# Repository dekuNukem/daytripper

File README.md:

# Daytripper: Hide-My-Windows Laser Tripwire

[Buy on Tindie](https://www.tindie.com/products/dekuNukem/daytripper-hide-my-windows-laser-tripwire/) | [Official Discord](https://discord.gg/VM4kbnf) | [Getting Started](quick_start_guide.md)

-----

Do you always slack off on your computer and worry about getting busted?

Not anymore because Daytripper is here to save the day!

Daytripper is a laser tripwire that can, upon triggering:

* Hide all your windows
* Lock your computer
* [Execute a custom script](/advanced_usage.md) to do whatever you want!

## Buy Daytripper on Tindie!

I did a small production run, and you can buy them directly on Tindie:

https://www.tindie.com/products/dekuNukem/daytripper

## How it Works

Daytripper comes in two parts: a Transmitter (TX) and a Receiver (RX).

Mount the TX in the path of incoming threat. Plug RX into your computer.

When motion is detected, RX will press `Win + M` and instantly hide what you're doing.

Alternatively, it can also lock your PC or [execute a custom script](/advanced_usage.md).

## Features

Daytripper...

* Can detect motion within 120cm (4 ft).

* Scan rate: 6Hz on battery, 30Hz while powered. Customisable with included software.

* Configurable parameters to suit your particular needs.

* 50-hour battery life, rechargeable via USB-C.

* Works out-of-box with Windows, compatible with all major OSs.

* 100 meter (330 ft) open-air communication range between TX and RX.

* Comes with a magnetic mounting kit.

* See [Quick Start Guide](https://github.com/dekuNukem/daytripper/blob/master/quick_start_guide.md) and [Advanced Usage Guide](https://github.com/dekuNukem/daytripper/blob/master/advanced_usage.md) for more details.

## Getting Started

If you received your Daytripper in kit form, follow this to put it together:

[Kit Assembly Guide](/assembly_guide.md)

For how to use Daytripper, see this:

[Quick Start Guide](/quick_start_guide.md)

For advanced features such as custom actions and adjusting settings, read this:

[Advanced Usage](/advanced_usage.md)

## Specification

## FAQ

### What operating system is supported?

Daytripper works out-of-box with Windows. No driver needed.

It is also compatible with anything that supports USB keyboards, such as Linux, MacOS, Android, and more.

Read [Advanced Usage Guide](/advanced_usage.md) to see how to use it on other systems.

### What is the range of Daytripper?

The laser ToF sensor can detect motion within 120cm (4 ft).

The wireless communication range between TX and RX should be around 100 meters (330 feet) open air. Might be less in indoor environments. 

### Battery life?

Around 50 hours (more than 2 days!) with default configuration.

Can be increased or decreased by adjusting settings.

Rechargeable via USB Type-C connector.

### Can I use it for purposes other than hiding windows?

Yes. It can also lock your computer, or perform a custom action.

See [Advanced Usage Guide](/advanced_usage.md).

## I Want One!

I did a small production run, and you can buy them directly on Tindie:

https://www.tindie.com/products/dekuNukem/daytripper

## Questions or Comments?

Please feel free to [open an issue](https://github.com/dekuNukem/duckypad/issues), ask in the [official Daytripper discord](https://discord.gg/VM4kbnf), DM me on discord `dekuNukem#6998`, or email `dekuNukem`@`gmail`.`com` for inquires.

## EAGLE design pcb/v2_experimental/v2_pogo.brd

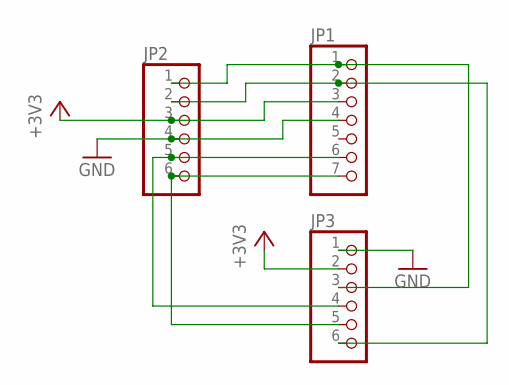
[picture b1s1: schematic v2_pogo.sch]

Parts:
JP1: PINHD-1X7; 1X07
JP2, JP3: PINHD-1X6; 1X06

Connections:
+3V3: JP1.3, JP2.3, JP3.2
GND: JP1.4, JP2.4, JP3.1
unnamed: JP1.7, JP2.6, JP3.5
unnamed: JP1.6, JP2.5, JP3.4
unnamed: JP1.2, JP2.2, JP3.6
unnamed: JP1.1, JP2.1, JP3.3

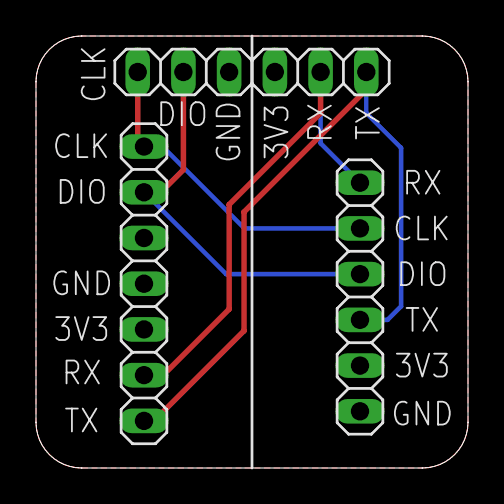
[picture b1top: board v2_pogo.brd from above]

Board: 2 copper layers, 24.0 x 24.0 mm, 3 parts (0 on the bottom side), 6 nets.

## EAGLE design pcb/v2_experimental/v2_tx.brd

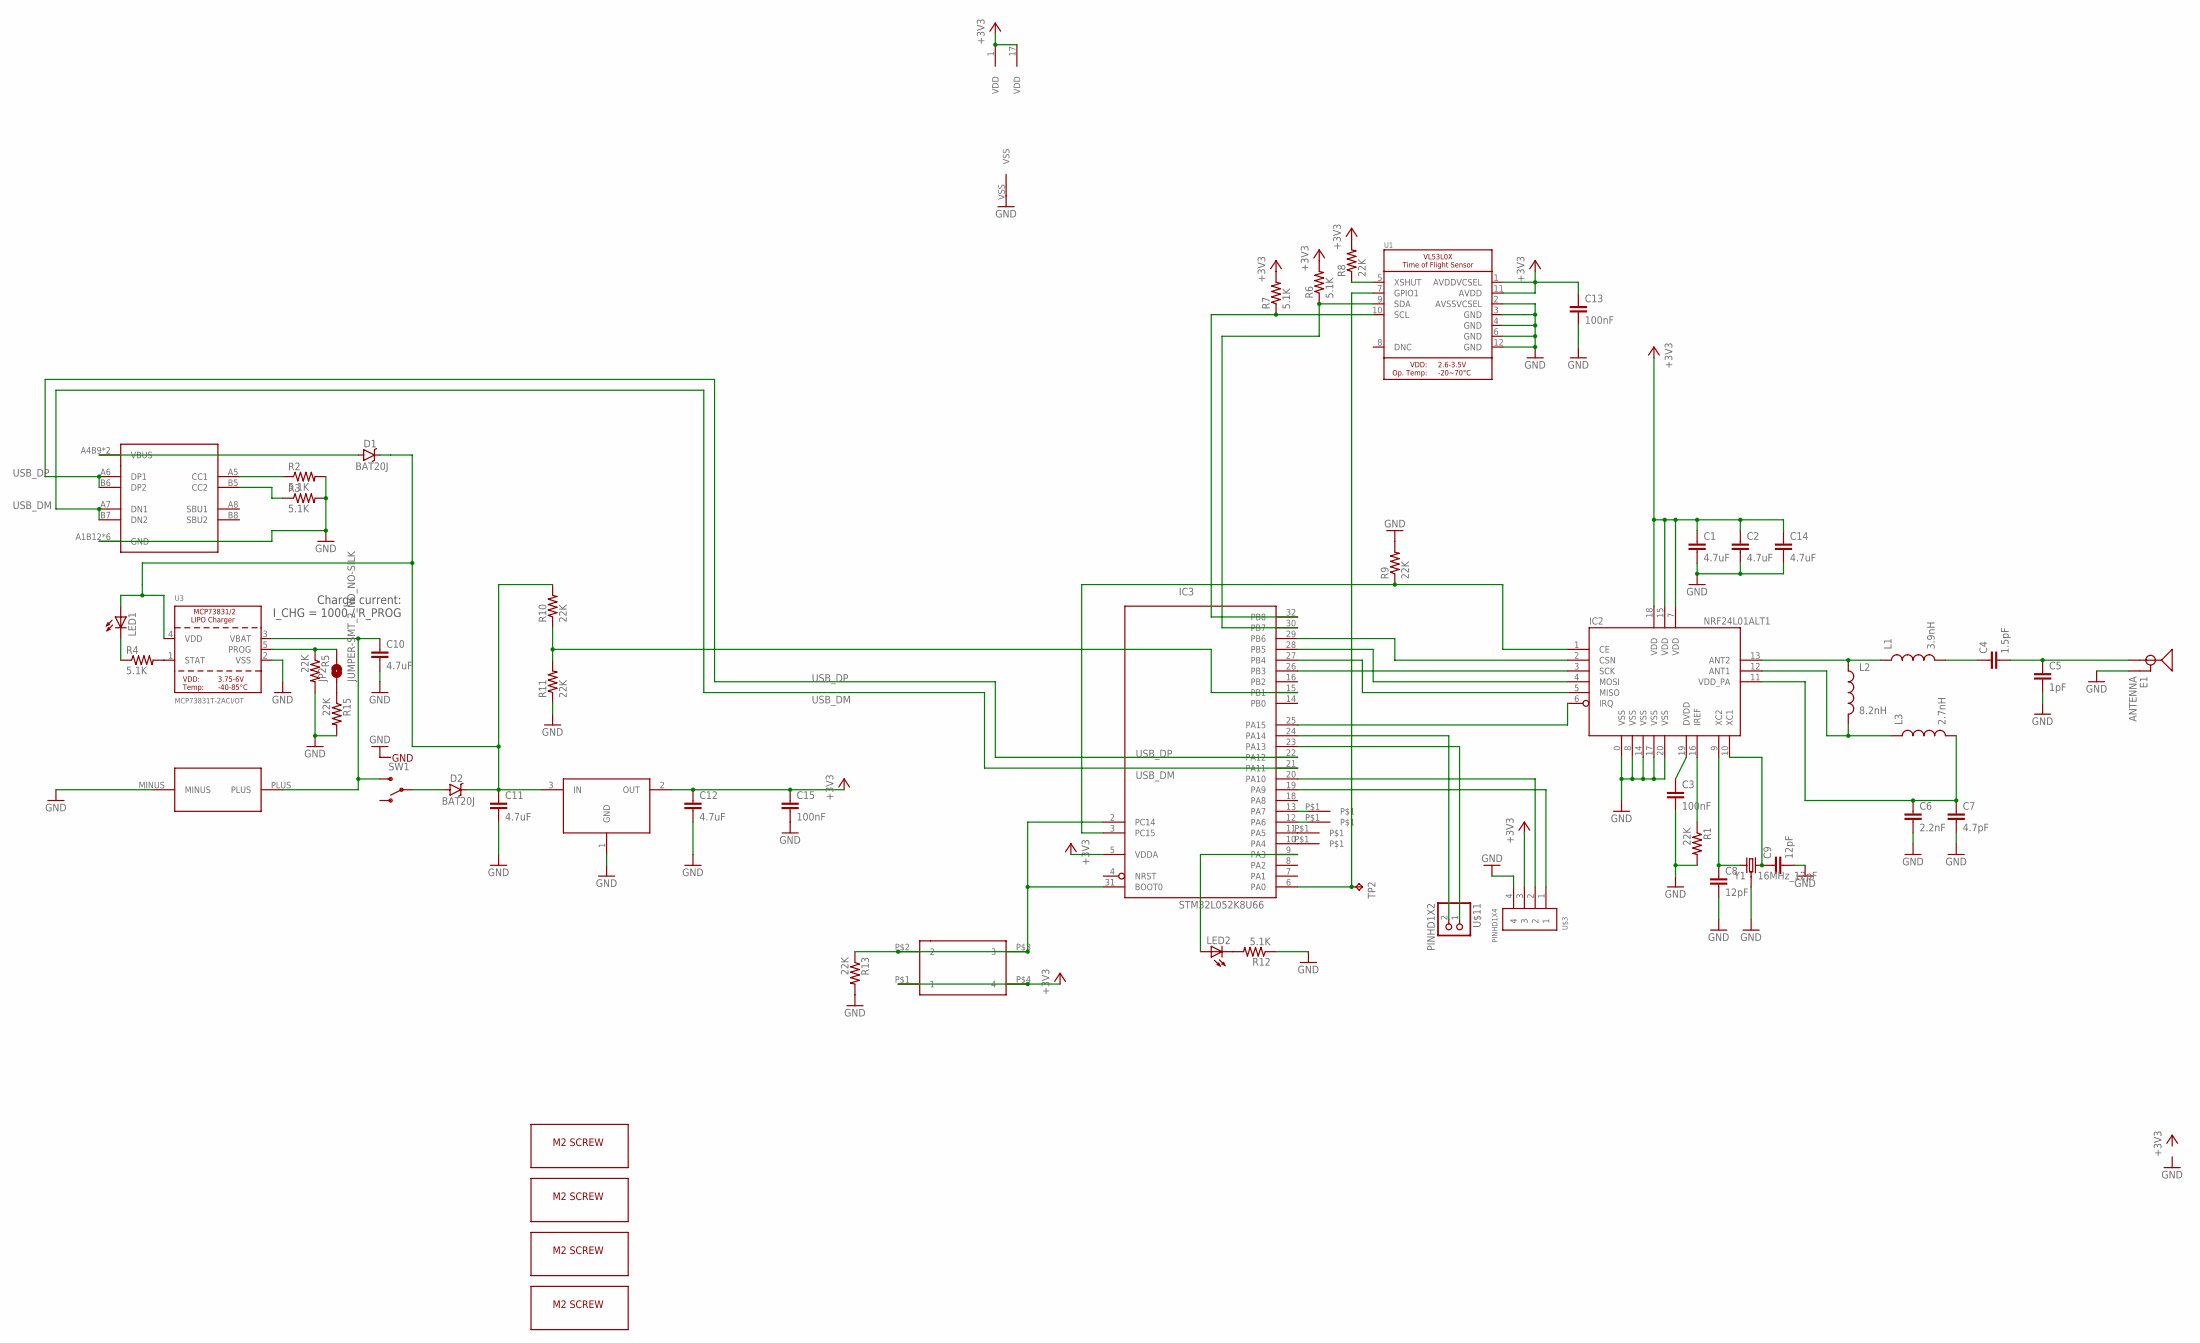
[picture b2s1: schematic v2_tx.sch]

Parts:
C1, C2, C10, C11, C12, C14: 4.7uF; 0805
C3, C13, C15: 100nF; 0805
C4: 1.5pF; 0805
C5: 1pF; 0805
C6: 2.2nF; 0805
C7: 4.7pF; 0805
C8, C9: 12pF; 0805
D1, D2: BAT20J; SOD-323
E1: ANTENNA; TRACE_ANTENNA_2.4GHZ_25.7MM_TUNED
IC2: NRF24L01ALT1; QFN20_ALT1
IC3: STM32L052K8U66; UFQFPN32
JP2: JUMPER-SMT_2_NO_NO-SILK; SMT-JUMPER_2_NO_NO-SILK
L1: 3.9nH; 0805
L2: 8.2nH; 0805
L3: 2.7nH; 0805
LED1, LED2: LEDCHIP-LED0805; CHIP-LED0805
R1, R5, R8, R9, R10, R11, R13, R15: 22K; 0805
R2, R3, R4, R6, R7, R12: 5.1K; 0805
SW1: SWITCH-SPDTTDFGDFG; SWITCH-SPST-SMD-A
SW2: 324_SW324_SWITCH_FOOT_HOLE; 342_SWICH_FOOT_HOLE
TP2: TPTP10R; TP10R
U1: VL53L0X; LGA12_ST
U2: USBC_16P; USBC_16P_FOOT
U3: MCP73831T-2ACI/OT; SOT23-5
U4: XC6206_DEV; SOT23R_INFINEON
U$1, U$12, U$13, U$14: M2_SCREW_DEV; M2_SCREW_FOOT
U$2: HOT_SWAP_COIN_BAT; COIN_BAT_HOTSWAP_SOCKET
U$3: PINHD1X4; 1X04-CLEANBIG
U$4, U$5, U$6, U$7: TESTPAD
U$11: PINHD1X2; 1X02
Y1: 16MHz_12pF; CRYSTAL-SMD-3.2X2.5MM

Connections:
+3V3: C1.1, C2.1, C12.1, C13.1, C14.1, C15.1, IC2.7 (VDD), IC2.15 (VDD), IC2.18 (VDD), IC3.1 (VDD), IC3.5 (VDDA), IC3.17 (VDD), R6.2, R7.2, R8.2, SW2.P$1 (1), SW2.P$4 (4), U1.1 (AVDDVCSEL), U1.11 (AVDD), U4.2 (OUT), U$3.3
GND: C1.2, C2.2, C3.2, C5.2, C6.2, C7.2, C8.2, C9.2, C10.2, C11.2, C12.2, C13.2, C14.2, C15.2, E1.GND, E1.GND2 (GND), IC2.0 (VSS), IC2.8 (VSS), IC2.14 (VSS), IC2.17 (VSS), IC2.20 (VSS), IC3.VSS, R1.2, R2.2, R3.2, R5.2, R9.2, R11.1, R12.1, R13.2, R15.2, SW1.G1 (GND), SW1.G2 (GND), SW1.G3 (GND), SW1.G4 (GND), U1.2 (AVSSVCSEL), U1.3 (GND), U1.4 (GND), U1.6 (GND), U1.12 (GND), U2.A1B12 (GND), U2.B11A12 (GND), U2.P$13 (GND), U2.P$14 (GND), U2.P$15 (GND), U2.P$16 (GND), U3.2 (VSS), U4.1 (GND), U$2.MINUS, U$3.4, Y1.2 (3), Y1.4 (3)
unnamed: C3.1, IC2.19 (DVDD)
unnamed: IC2.16 (IREF), R1.1
unnamed: IC2.13 (ANT2), L1.1, L2.1
unnamed: C4.1, L1.2
unnamed: C4.2, C5.1, E1.ANT (SIGNAL)
unnamed: IC2.12 (ANT1), L2.2, L3.1
unnamed: C8.1, IC2.9 (XC2), Y1.1
unnamed: C6.1, C7.1, IC2.11 (VDD_PA), L3.2
unnamed: C9.1, IC2.10 (XC1), Y1.3 (2)
unnamed: R3.1, U2.B5 (CC2)
unnamed: R2.1, U2.A5 (CC1)
unnamed: LED1.C, R4.1
unnamed: R4.2, U3.1 (STAT)
unnamed: IC2.4 (MOSI), IC3.28 (PB5)
unnamed: IC2.5 (MISO), IC3.27 (PB4)
unnamed: IC2.3 (SCK), IC3.26 (PB3)
unnamed: JP2.2, R5.1, U3.5 (PROG)
unnamed: IC3.24 (PA14), U$11.2
unnamed: D2.A, SW1.2
unnamed: IC2.2 (CSN), IC3.29 (PB6)
unnamed: IC2.1 (CE), IC3.3 (PC15), R9.1
unnamed: IC2.6 (IRQ), IC3.25 (PA15)
unnamed: IC3.9 (PA3), LED2.A
unnamed: R8.1, U1.5 (XSHUT)
unnamed: C10.1, SW1.3 (S), U3.3 (VBAT), U$2.PLUS
unnamed: D1.A, U2.A4B9 (VBUS), U2.B4A9 (VBUS)
unnamed: C11.1, D1.C, D2.C, LED1.A, R10.2, U3.4 (VDD), U4.3 (IN)
unnamed: LED2.C, R12.2
unnamed: IC3.23 (PA13), U$11.1
unnamed: IC3.2 (PC14), IC3.31 (BOOT0), R13.1, SW2.P$2 (2), SW2.P$3 (3)
unnamed: IC3.20 (PA10), U$3.2
unnamed: IC3.19 (PA9), U$3.1
unnamed: IC3.10 (PA4), U$5.P$1
unnamed: IC3.11 (PA5), U$4.P$1
unnamed: IC3.15 (PB1), R10.1, R11.2
unnamed: IC3.6 (PA0), TP2.TP, U1.7 (GPIO1)
unnamed: IC3.12 (PA6), U$7.P$1
unnamed: JP2.1, R15.1
unnamed: IC3.32 (PB8), R7.1, U1.10 (SCL)
unnamed: IC3.30 (PB7), R6.1, U1.9 (SDA)
unnamed: IC3.13 (PA7), U$6.P$1
USB_DM: IC3.21 (PA11), U2.A7 (DN1), U2.B7 (DN2)
USB_DP: IC3.22 (PA12), U2.A6 (DP1), U2.B6 (DP2)

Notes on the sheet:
Charge current: I_CHG = 1000 / R_PROG

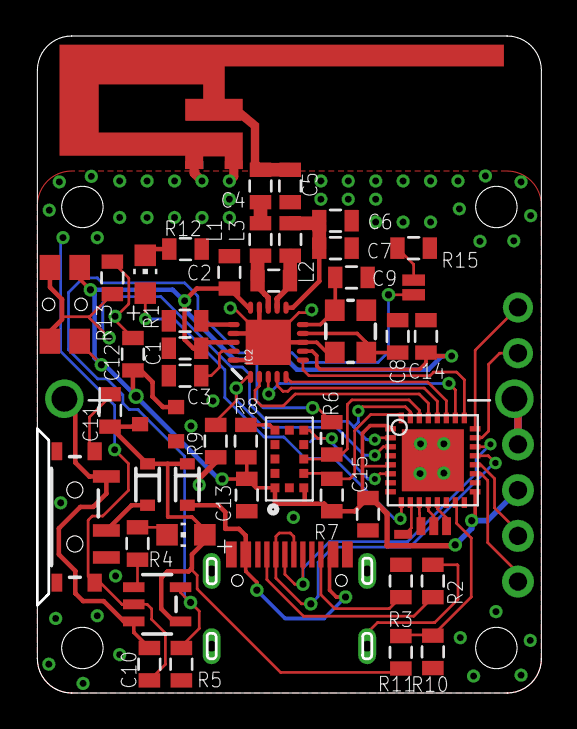
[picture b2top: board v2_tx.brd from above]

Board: 2 copper layers, 28.0 x 36.5 mm, 59 parts (1 on the bottom side), 45 nets.

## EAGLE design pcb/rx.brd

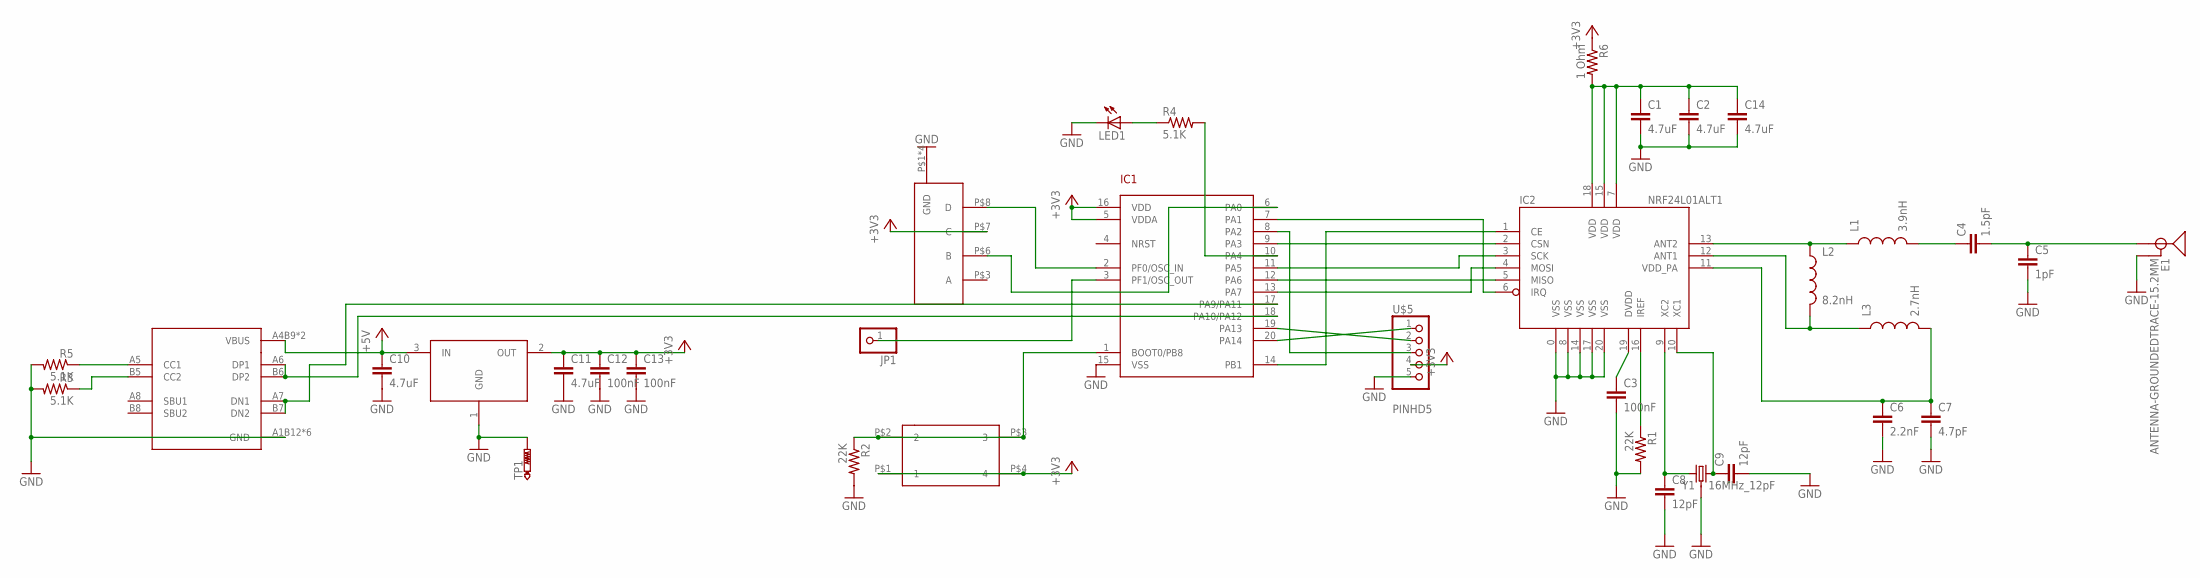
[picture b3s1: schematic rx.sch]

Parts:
C1, C2, C10, C11, C14: 4.7uF; 0805
C3, C12, C13: 100nF; 0805
C4: 1.5pF; 0805
C5: 1pF; 0805
C6: 2.2nF; 0805
C7: 4.7pF; 0805
C8, C9: 12pF; 0805
E1: ANTENNA-GROUNDEDTRACE-15.2MM; TRACE_ANTENNA_2.4GHZ_15.2MM
IC1: STM32F042F4; TSSOP20
IC2: NRF24L01ALT1; QFN20_ALT1
JP1: PINHD-1X1CB; 1X01-CLEANBIG
L1: 3.9nH; 0805
L2: 8.2nH; 0805
L3: 2.7nH; 0805
LED1: LEDCHIP-LED0805; CHIP-LED0805
R1, R2: 22K; 0805
R3, R4, R5: 5.1K; 0805
R6: 1 Ohm; 0805
SW1: SW_3POS_DEVSW_3POS_OFFICIAL; SW_3POS_FOOT_OFFICIAL
SW2: 324_SW324_SWITCH_FOOT_HOLE; 342_SWICH_FOOT_HOLE
TP1: PTR1TP18R; TP18R
U1: USBC_16P; USBC_16P_FOOT
U2: XC6206_DEV; SOT23R_INFINEON
U$5: PINHD5; 1X05
Y1: 16MHz_12pF; CRYSTAL-SMD-3.2X2.5MM

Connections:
+3V3: C11.1, C12.1, C13.1, IC1.5 (VDDA), IC1.16 (VDD), R6.1, SW1.P$7 (C), SW2.P$1 (1), SW2.P$4 (4), U2.2 (OUT), U$5.4
+5V: C10.1, U1.A4B9 (VBUS), U1.B4A9 (VBUS), U2.3 (IN)
GND: C1.2, C2.2, C3.2, C5.2, C6.2, C7.2, C8.2, C9.2, C10.2, C11.2, C12.2, C13.2, C14.2, E1.GND, IC1.15 (VSS), IC2.0 (VSS), IC2.8 (VSS), IC2.14 (VSS), IC2.17 (VSS), IC2.20 (VSS), LED1.C, R1.2, R2.2, R3.2, R5.2, SW1.P$1 (GND), SW1.P$2 (GND), SW1.P$4 (GND), SW1.P$5 (GND), TP1.TP, U1.A1B12 (GND), U1.B11A12 (GND), U1.P$13 (GND), U1.P$14 (GND), U1.P$15 (GND), U1.P$16 (GND), U2.1 (GND), U$5.5, Y1.2 (3), Y1.4 (3)
unnamed: C3.1, IC2.19 (DVDD)
unnamed: IC2.16 (IREF), R1.1
unnamed: IC2.13 (ANT2), L1.1, L2.1
unnamed: C4.1, L1.2
unnamed: C4.2, C5.1, E1.ANT (SIGNAL)
unnamed: IC2.12 (ANT1), L2.2, L3.1
unnamed: C8.1, IC2.9 (XC2), Y1.1
unnamed: C6.1, C7.1, IC2.11 (VDD_PA), L3.2
unnamed: C9.1, IC2.10 (XC1), Y1.3 (2)
unnamed: IC1.2 (PF0/OSC_IN), SW1.P$8 (D)
unnamed: IC1.1 (BOOT0/PB8), R2.1, SW2.P$2 (2), SW2.P$3 (3)
unnamed: IC1.17 (PA9/PA11), U1.A7 (DN1), U1.B7 (DN2)
unnamed: IC1.18 (PA10/PA12), U1.A6 (DP1), U1.B6 (DP2)
unnamed: IC1.12 (PA6), IC2.5 (MISO)
unnamed: IC1.13 (PA7), IC2.4 (MOSI)
unnamed: IC1.11 (PA5), IC2.3 (SCK)
unnamed: IC1.19 (PA13), U$5.2
unnamed: LED1.A, R4.1
unnamed: IC1.3 (PF1/OSC_OUT), JP1.1
unnamed: IC1.20 (PA14), U$5.1
unnamed: IC1.8 (PA2), U$5.3
unnamed: IC1.14 (PB1), IC2.1 (CE)
unnamed: IC1.10 (PA4), R4.2
unnamed: IC1.9 (PA3), IC2.2 (CSN)
unnamed: R3.1, U1.B5 (CC2)
unnamed: IC1.6 (PA0), SW1.P$6 (B)
unnamed: R5.1, U1.A5 (CC1)
unnamed: C1.1, C2.1, C14.1, IC2.7 (VDD), IC2.15 (VDD), IC2.18 (VDD), R6.2
unnamed: IC1.7 (PA1), IC2.6 (IRQ)

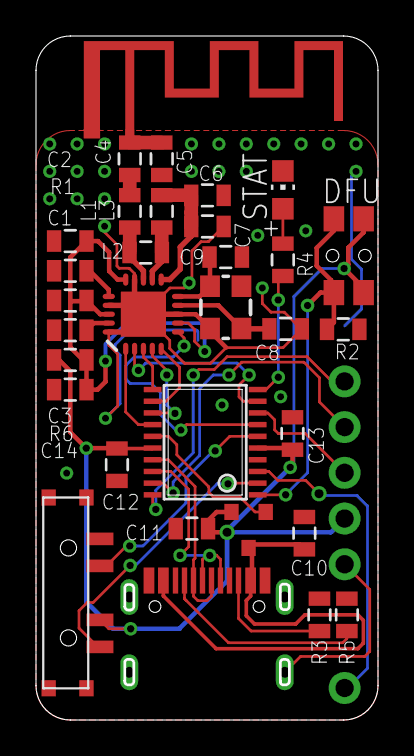
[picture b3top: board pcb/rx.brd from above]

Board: 2 copper layers, 19.0 x 38.0 mm, 35 parts (1 on the bottom side), 32 nets.

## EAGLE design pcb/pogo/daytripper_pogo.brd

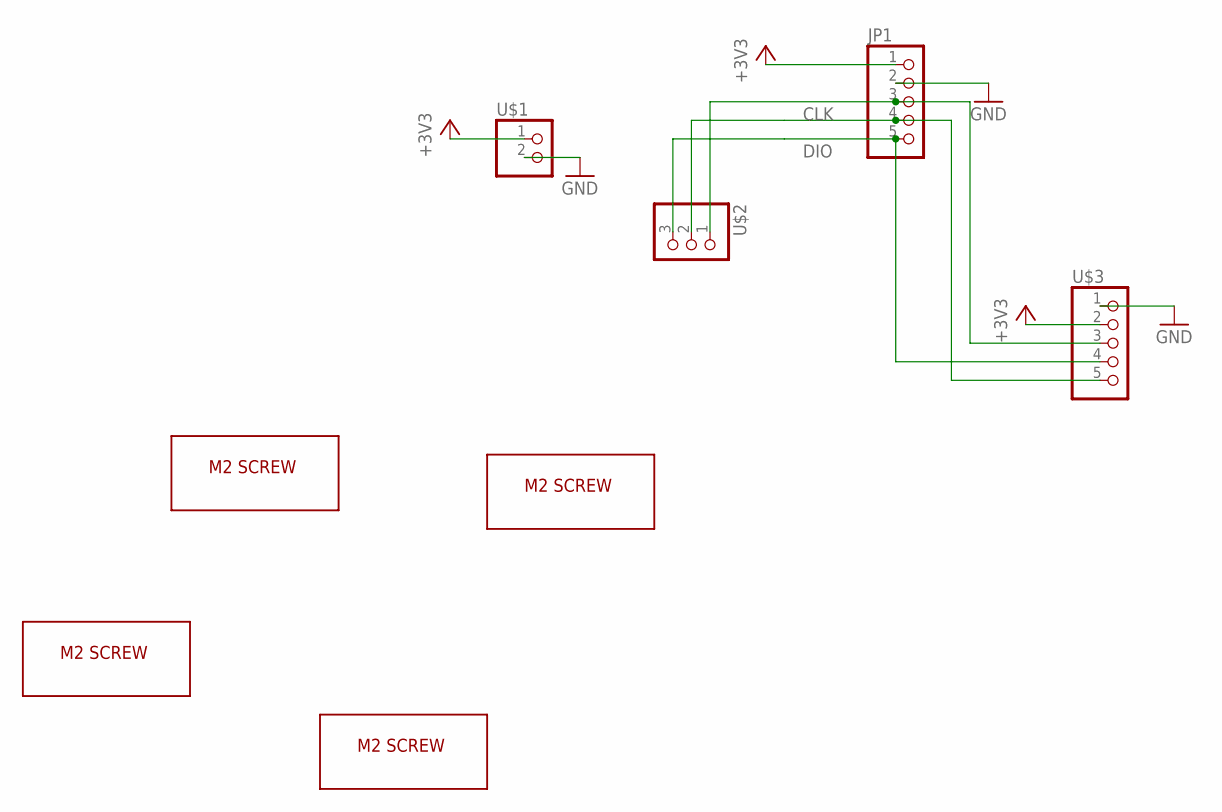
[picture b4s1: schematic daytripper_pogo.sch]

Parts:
JP1: PINHD-1X5; 1X05
U$1: POGO-1X2; 1X02
U$2: POGO-1X3; 1X03
U$3: POGO-1X5; 1X05
U$4, U$12, U$13, U$14: M2_SCREW_DEV; M2_SCREW_FOOT

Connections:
+3V3: JP1.1, U$1.1, U$3.2
CLK: JP1.4, U$2.2, U$3.5
DIO: JP1.5, U$2.3, U$3.4
GND: JP1.2, U$1.2, U$3.1
unnamed: JP1.3, U$2.1, U$3.3

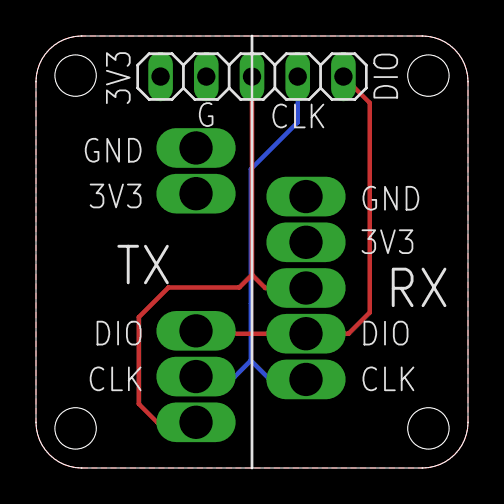
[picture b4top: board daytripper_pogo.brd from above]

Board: 2 copper layers, 24.0 x 24.0 mm, 8 parts (0 on the bottom side), 5 nets.

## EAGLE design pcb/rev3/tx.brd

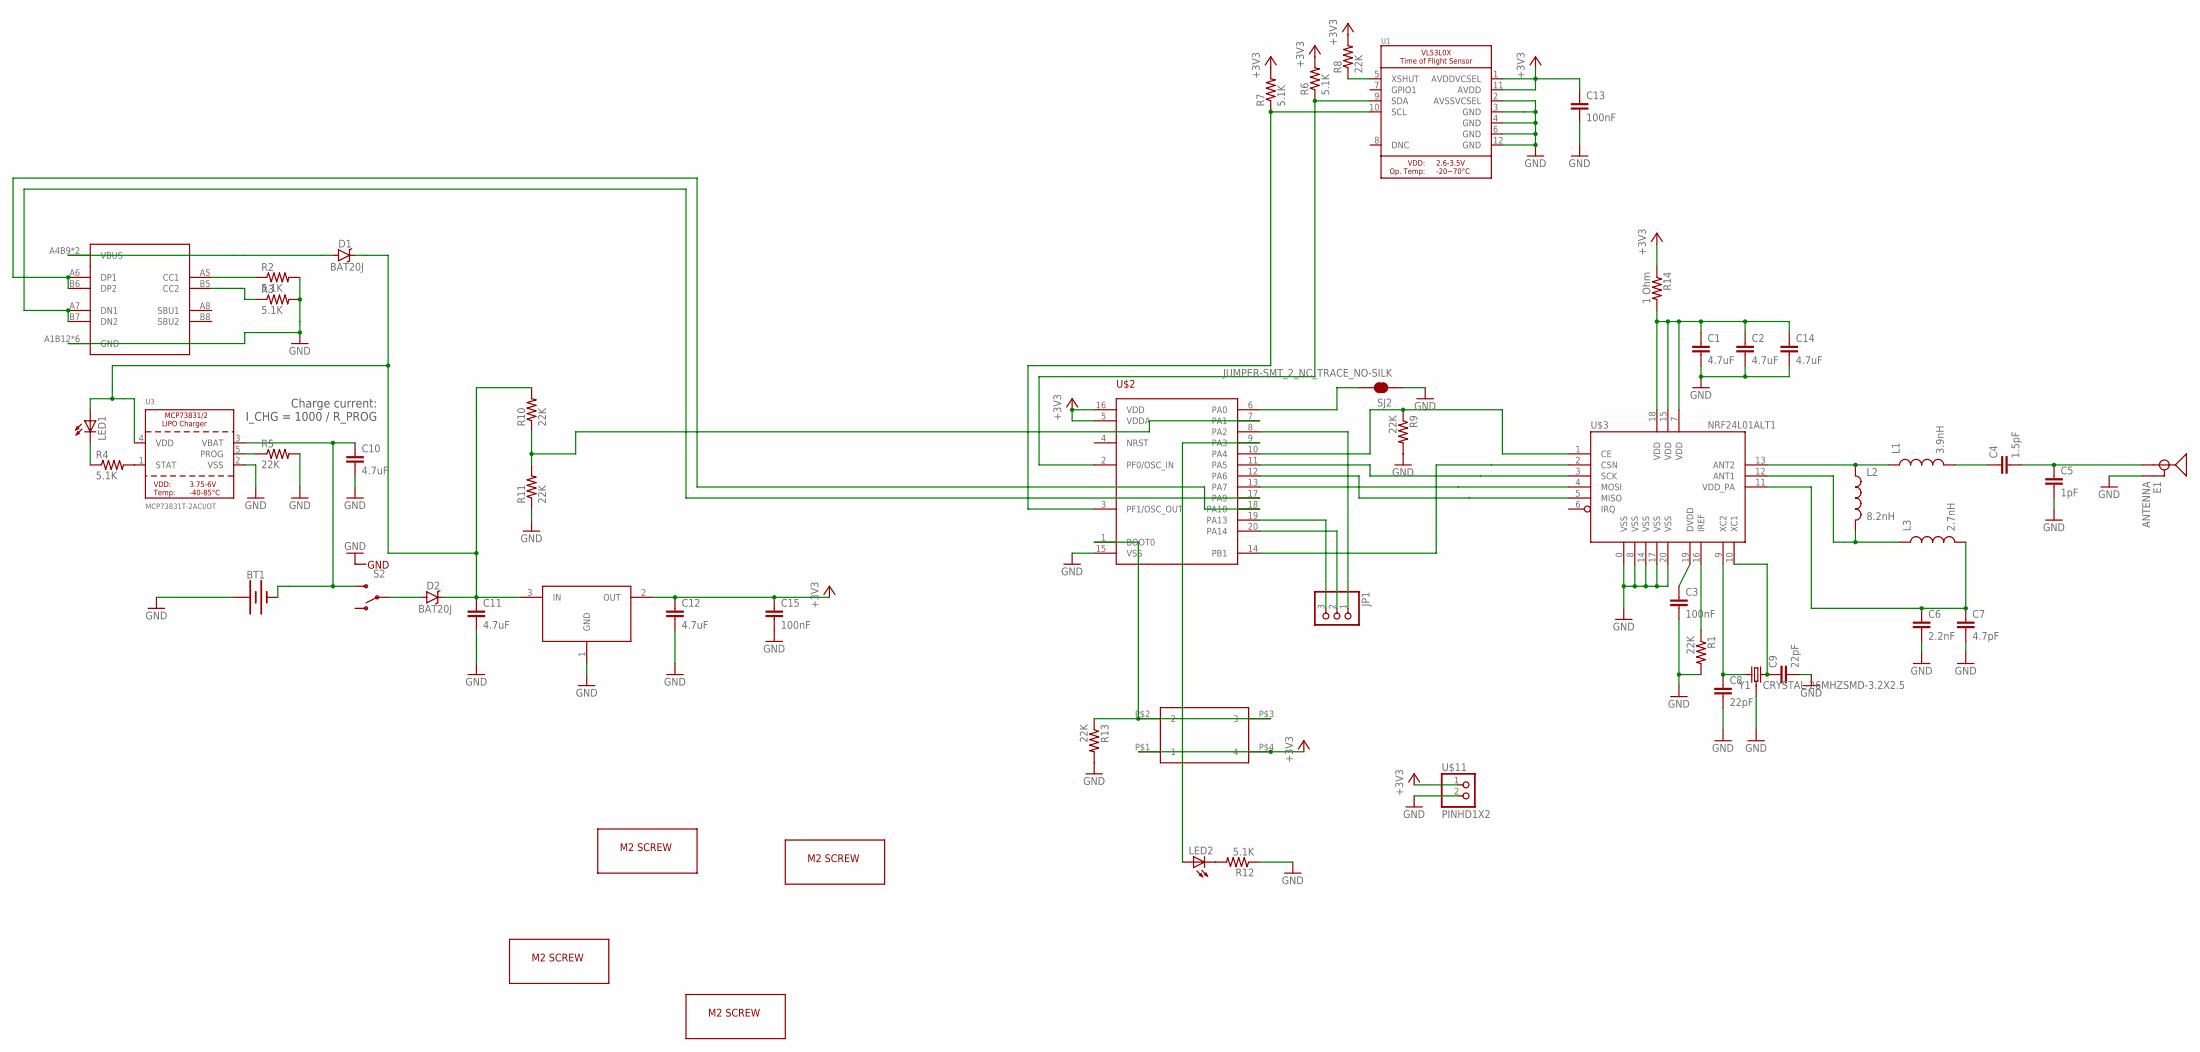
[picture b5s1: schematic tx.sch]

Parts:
BT1: TX_SPARKFUN-BATTERIES_BATTERY-24.5MM_PTH; TX_SPARKFUN-BATTERIES_BATTCON_24.5MM_PTH
C1, C2, C10, C11, C12, C14: 4.7uF; 0805
C3, C13, C15: 100nF; 0805
C4: 1.5pF; 0805
C5: 1pF; 0805
C6: 2.2nF; 0805
C7: 4.7pF; 0805
C8, C9: 22pF; 0805
D1, D2: BAT20J; SOD-323
E1: ANTENNA; TRACE_ANTENNA_2.4GHZ_25.7MM_TUNED
JP1: PINHD-1X3CB; 1X03-CLEANBIG
L1: 3.9nH; 0805
L2: 8.2nH; 0805
L3: 2.7nH; 0805
LED1, LED2: LEDCHIP-LED0805; CHIP-LED0805
R1, R5, R8, R9, R10, R11, R13: 22K; 0805
R2, R3, R4, R6, R7, R12: 5.1K; 0805
R14: 1 Ohm; 0805
S2: SWITCH-SPDTTDFGDFG; SWITCH-SPST-SMD-A
SJ2: JUMPER-SMT_2_NC_TRACE_NO-SILK; SMT-JUMPER_2_NC_TRACE_NO-SILK
U1: VL53L0X; LGA12_ST
U3: MCP73831T-2ACI/OT; SOT23-5
U$1, U$12, U$13, U$14: M2_SCREW_DEV; M2_SCREW_FOOT
U$2: STM32F030F4; TSSOP20
U$3: NRF24L01ALT1; QFN20_ALT1
U$4: USBC_16P; USBC_16P_FOOT
U$9: XC6206_DEV; SOT23R_INFINEON
U$10: 324_SW324_SWITCH_FOOT_HOLE; 342_SWICH_FOOT_HOLE
U$11: PINHD1X2; 1X02
Y1: CRYSTAL-26MHZSMD-3.2X2.5; CRYSTAL-SMD-3.2X2.5MM

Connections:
+3V3: C12.1, C13.1, C15.1, R6.2, R7.2, R8.2, R14.1, U1.1 (AVDDVCSEL), U1.11 (AVDD), U$2.5 (VDDA), U$2.16 (VDD), U$9.2 (OUT), U$10.P$1 (1), U$10.P$4 (4), U$11.1
GND: BT1.2 (+), C1.2, C2.2, C3.2, C5.2, C6.2, C7.2, C8.2, C9.2, C10.2, C11.2, C12.2, C13.2, C14.2, C15.2, E1.GND, E1.GND2 (GND), R1.2, R2.2, R3.2, R5.2, R9.2, R11.1, R12.1, R13.2, S2.G1 (GND), S2.G2 (GND), S2.G3 (GND), S2.G4 (GND), SJ2.1, U1.2 (AVSSVCSEL), U1.3 (GND), U1.4 (GND), U1.6 (GND), U1.12 (GND), U3.2 (VSS), U$2.15 (VSS), U$3.0 (VSS), U$3.8 (VSS), U$3.14 (VSS), U$3.17 (VSS), U$3.20 (VSS), U$4.A1B12 (GND), U$4.B11A12 (GND), U$4.P$13 (GND), U$4.P$14 (GND), U$4.P$15 (GND), U$4.P$16 (GND), U$9.1 (GND), U$11.2, Y1.2 (3), Y1.4 (3)
unnamed: C3.1, U$3.19 (DVDD)
unnamed: R1.1, U$3.16 (IREF)
unnamed: L1.1, L2.1, U$3.13 (ANT2)
unnamed: C4.1, L1.2
unnamed: C4.2, C5.1, E1.ANT (SIGNAL)
unnamed: L2.2, L3.1, U$3.12 (ANT1)
unnamed: C8.1, U$3.9 (XC2), Y1.1
unnamed: C6.1, C7.1, L3.2, U$3.11 (VDD_PA)
unnamed: C9.1, U$3.10 (XC1), Y1.3 (2)
unnamed: R3.1, U$4.B5 (CC2)
unnamed: R2.1, U$4.A5 (CC1)
unnamed: LED1.C, R4.1
unnamed: R4.2, U3.1 (STAT)
unnamed: U$2.13 (PA7), U$3.4 (MOSI)
unnamed: U$2.12 (PA6), U$3.5 (MISO)
unnamed: U$2.11 (PA5), U$3.3 (SCK)
unnamed: R5.1, U3.5 (PROG)
unnamed: U$2.18 (PA10), U$4.A6 (DP1), U$4.B6 (DP2)
unnamed: D2.A, S2.2
unnamed: U$2.14 (PB1), U$3.2 (CSN)
unnamed: R9.1, U$2.10 (PA4), U$3.1 (CE)
unnamed: R7.1, U1.10 (SCL), U$2.3 (PF1/OSC_OUT)
unnamed: R6.1, U1.9 (SDA), U$2.2 (PF0/OSC_IN)
unnamed: R8.1, U1.5 (XSHUT)
unnamed: BT1.1 (-), C10.1, S2.3 (S), U3.3 (VBAT)
unnamed: D1.A, U$4.A4B9 (VBUS), U$4.B4A9 (VBUS)
unnamed: C11.1, D1.C, D2.C, LED1.A, R10.2, U3.4 (VDD), U$9.3 (IN)
unnamed: LED2.C, R12.2
unnamed: LED2.A, U$2.9 (PA3)
unnamed: R13.1, U$2.1 (BOOT0), U$10.P$2 (2), U$10.P$3 (3)
unnamed: JP1.3, U$2.19 (PA13)
unnamed: JP1.2, U$2.20 (PA14)
unnamed: JP1.1, U$2.8 (PA2)
unnamed: U$2.17 (PA9), U$4.A7 (DN1), U$4.B7 (DN2)
unnamed: R10.1, R11.2, U$2.7 (PA1)
unnamed: SJ2.2, U$2.6 (PA0)
unnamed: C1.1, C2.1, C14.1, R14.2, U$3.7 (VDD), U$3.15 (VDD), U$3.18 (VDD)

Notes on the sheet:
Charge current: I_CHG = 1000 / R_PROG

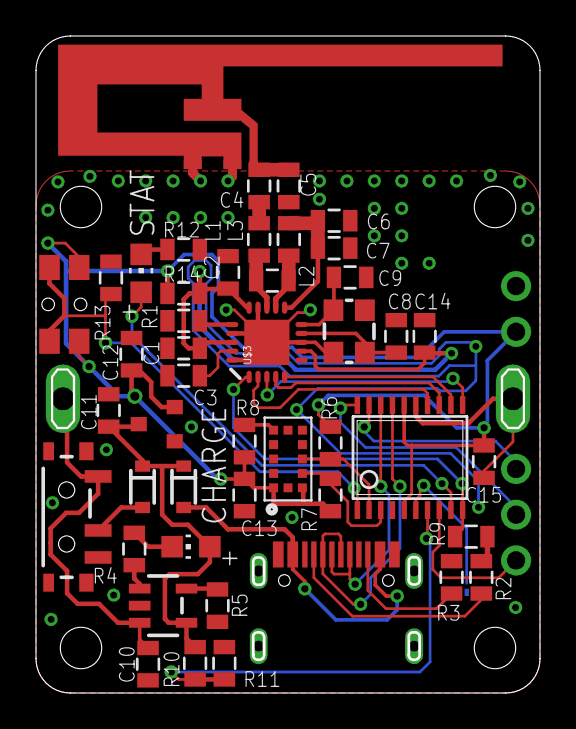
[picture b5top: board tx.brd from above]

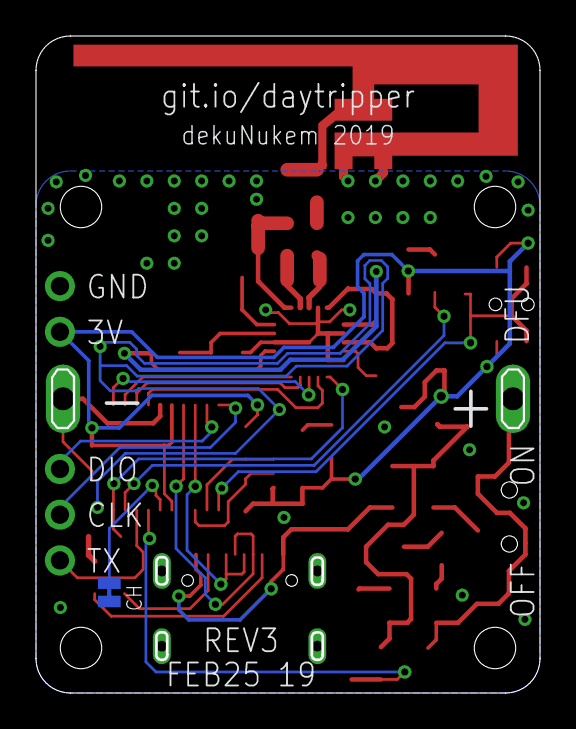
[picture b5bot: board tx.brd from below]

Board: 2 copper layers, 28.0 x 36.5 mm, 54 parts (2 on the bottom side), 39 nets.

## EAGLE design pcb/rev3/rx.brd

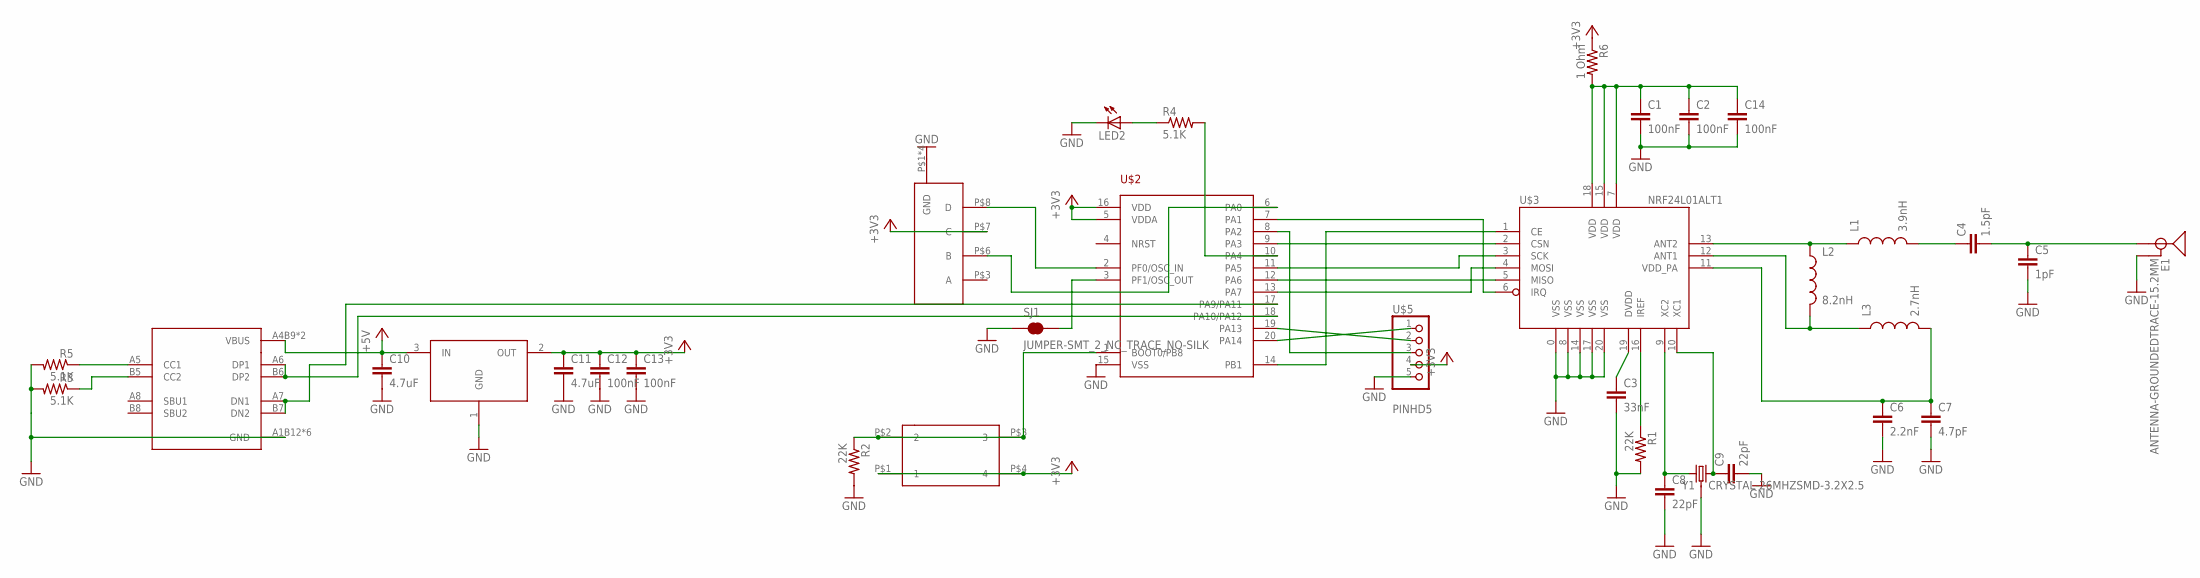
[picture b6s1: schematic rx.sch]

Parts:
C1, C2, C12, C13, C14: 100nF; 0805
C3: 33nF; 0805
C4: 1.5pF; 0805
C5: 1pF; 0805
C6: 2.2nF; 0805
C7: 4.7pF; 0805
C8, C9: 22pF; 0805
C10, C11: 4.7uF; 0805
E1: ANTENNA-GROUNDEDTRACE-15.2MM; TRACE_ANTENNA_2.4GHZ_15.2MM
L1: 3.9nH; 0805
L2: 8.2nH; 0805
L3: 2.7nH; 0805
LED2: LEDCHIP-LED0805; CHIP-LED0805
R1, R2: 22K; 0805
R3, R4, R5: 5.1K; 0805
R6: 1 Ohm; 0805
SJ1: JUMPER-SMT_2_NC_TRACE_NO-SILK; SMT-JUMPER_2_NC_TRACE_NO-SILK
U$1: SW_3POS_DEVSW_3POS_OFFICIAL; SW_3POS_FOOT_OFFICIAL
U$2: STM32F042F4; TSSOP20
U$3: NRF24L01ALT1; QFN20_ALT1
U$4: XC6206_DEV; SOT23R_INFINEON
U$5: PINHD5; 1X05
U$6: USBC_16P; USBC_16P_FOOT
U$10: 324_SW324_SWITCH_FOOT_HOLE; 342_SWICH_FOOT_HOLE
Y1: CRYSTAL-26MHZSMD-3.2X2.5; CRYSTAL-SMD-3.2X2.5MM

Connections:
+3V3: C11.1, C12.1, C13.1, R6.1, U$1.P$7 (C), U$2.5 (VDDA), U$2.16 (VDD), U$4.2 (OUT), U$5.4, U$10.P$1 (1), U$10.P$4 (4)
+5V: C10.1, U$4.3 (IN), U$6.A4B9 (VBUS), U$6.B4A9 (VBUS)
GND: C1.2, C2.2, C3.2, C5.2, C6.2, C7.2, C8.2, C9.2, C10.2, C11.2, C12.2, C13.2, C14.2, E1.GND, LED2.C, R1.2, R2.2, R3.2, R5.2, SJ1.1, U$1.P$1 (GND), U$1.P$2 (GND), U$1.P$4 (GND), U$1.P$5 (GND), U$2.15 (VSS), U$3.0 (VSS), U$3.8 (VSS), U$3.14 (VSS), U$3.17 (VSS), U$3.20 (VSS), U$4.1 (GND), U$5.5, U$6.A1B12 (GND), U$6.B11A12 (GND), U$6.P$13 (GND), U$6.P$14 (GND), U$6.P$15 (GND), U$6.P$16 (GND), Y1.2 (3), Y1.4 (3)
unnamed: C3.1, U$3.19 (DVDD)
unnamed: R1.1, U$3.16 (IREF)
unnamed: L1.1, L2.1, U$3.13 (ANT2)
unnamed: C4.1, L1.2
unnamed: C4.2, C5.1, E1.ANT (SIGNAL)
unnamed: L2.2, L3.1, U$3.12 (ANT1)
unnamed: C8.1, U$3.9 (XC2), Y1.1
unnamed: C6.1, C7.1, L3.2, U$3.11 (VDD_PA)
unnamed: C9.1, U$3.10 (XC1), Y1.3 (2)
unnamed: U$1.P$8 (D), U$2.2 (PF0/OSC_IN)
unnamed: R2.1, U$2.1 (BOOT0/PB8), U$10.P$2 (2), U$10.P$3 (3)
unnamed: U$2.17 (PA9/PA11), U$6.A7 (DN1), U$6.B7 (DN2)
unnamed: U$2.18 (PA10/PA12), U$6.A6 (DP1), U$6.B6 (DP2)
unnamed: U$2.12 (PA6), U$3.5 (MISO)
unnamed: U$2.13 (PA7), U$3.4 (MOSI)
unnamed: U$2.11 (PA5), U$3.3 (SCK)
unnamed: U$2.19 (PA13), U$5.2
unnamed: LED2.A, R4.1
unnamed: SJ1.2, U$2.3 (PF1/OSC_OUT)
unnamed: U$2.20 (PA14), U$5.1
unnamed: U$2.8 (PA2), U$5.3
unnamed: U$2.14 (PB1), U$3.1 (CE)
unnamed: R4.2, U$2.10 (PA4)
unnamed: U$2.9 (PA3), U$3.2 (CSN)
unnamed: R3.1, U$6.B5 (CC2)
unnamed: U$1.P$6 (B), U$2.6 (PA0)
unnamed: R5.1, U$6.A5 (CC1)
unnamed: C1.1, C2.1, C14.1, R6.2, U$3.7 (VDD), U$3.15 (VDD), U$3.18 (VDD)
unnamed: U$2.7 (PA1), U$3.6 (IRQ)

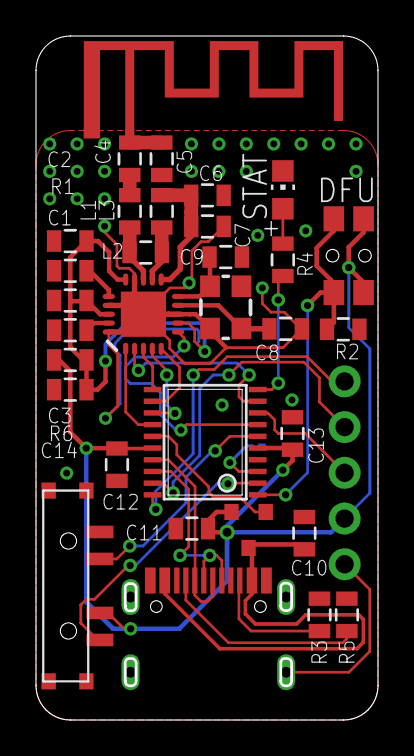
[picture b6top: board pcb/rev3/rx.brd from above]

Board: 2 copper layers, 19.0 x 38.0 mm, 34 parts (1 on the bottom side), 32 nets.

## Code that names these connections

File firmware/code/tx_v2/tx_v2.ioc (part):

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Mcu.Name=STM32L052K(6-8)Ux
Mcu.Package=UFQFPN32
Mcu.UserName=STM32L052K8Ux
PA0.GPIOParameters=GPIO_Label
PA0.GPIO_Label=TOF_INT
PA0.Signal=GPIO_Input
PA10.Mode=Asynchronous
PA10.Signal=USART1_RX
PA11.Mode=Device
PA11.Signal=USB_DM
PA12.Mode=Device
PA12.Signal=USB_DP
PA13.Mode=Serial_Wire
PA13.Signal=SYS_SWDIO
PA14.Mode=Serial_Wire
PA14.Signal=SYS_SWCLK
PA15.GPIOParameters=GPIO_Label
PA15.GPIO_Label=NRF_INT
PA15.Signal=GPIO_Input
PA3.GPIOParameters=GPIO_Label
PA3.GPIO_Label=USER_LED
PA3.Signal=S_TIM2_CH4
PA9.Mode=Asynchronous
PA9.Signal=USART1_TX
PB1.GPIOParameters=GPIO_Label
PB1.GPIO_Label=VBAT_ADC
PB1.Mode=IN9
PB1.Signal=ADC_IN9
PB3.Mode=Full_Duplex_Master
PB3.Signal=SPI1_SCK
PB4.Mode=Full_Duplex_Master
PB4.Signal=SPI1_MISO
PB5.Mode=Full_Duplex_Master
PB5.Signal=SPI1_MOSI
PB6.GPIOParameters=GPIO_Label
PB6.GPIO_Label=SPI1_CS
PB6.Signal=GPIO_Output
PB7.Mode=I2C
PB7.Signal=I2C1_SDA
PB8.Mode=I2C
PB8.Signal=I2C1_SCL
PC14-OSC32_IN.GPIOParameters=GPIO_Label
PC14-OSC32_IN.GPIO_Label=USER_BUTTON
PC14-OSC32_IN.Signal=GPIO_Input
PC15-OSC32_OUT.GPIOParameters=GPIO_Label
PC15-OSC32_OUT.GPIO_Label=NRF_CE
PC15-OSC32_OUT.Signal=GPIO_Output
RCC.SYSCLKFreq_VALUE=32000000
RCC.SYSCLKSource=RCC_SYSCLKSOURCE_PLLCLK
board=custom

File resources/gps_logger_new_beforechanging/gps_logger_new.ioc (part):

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Mcu.Name=STM32F042K6Tx
Mcu.Package=LQFP32
Mcu.UserName=STM32F042K6Tx
PA0.GPIOParameters=GPIO_Label
PA0.GPIO_Label=VBAT_DIV2
PA0.Mode=IN0
PA0.Signal=ADC_IN0
PA1.GPIOParameters=GPIO_Label
PA1.GPIO_Label=SD_LED
PA1.Signal=GPIO_Output
PA10.Mode=Asynchronous
PA10.Signal=USART1_RX
PA13.Mode=Serial_Wire
PA13.Signal=SYS_SWDIO
PA14.Mode=Serial_Wire
PA14.Signal=SYS_SWCLK
PA2.Mode=Asynchronous
PA2.Signal=USART2_TX
PA3.Mode=Asynchronous
PA3.Signal=USART2_RX
PA4.GPIOParameters=PinState,GPIO_Label
PA4.GPIO_Label=GPS_INT
PA4.PinState=GPIO_PIN_SET
PA4.Signal=GPIO_Output
PA5.Mode=Full_Duplex_Master
PA5.Signal=SPI1_SCK
PA6.Mode=Full_Duplex_Master
PA6.Signal=SPI1_MISO
PA7.Mode=Full_Duplex_Master
PA7.Signal=SPI1_MOSI
PA8.GPIOParameters=GPIO_PuPd,GPIO_Label
PA8.GPIO_Label=ACC_INT
PA8.GPIO_PuPd=GPIO_PULLDOWN
PA8.Signal=GPXTI8
PA9.Mode=Asynchronous
PA9.Signal=USART1_TX
PB0.GPIOParameters=PinState,GPIO_Label
PB0.GPIO_Label=SD_CS
PB0.PinState=GPIO_PIN_SET
PB0.Signal=GPIO_Output
PB1.GPIOParameters=GPIO_PuPd,GPIO_Label
PB1.GPIO_Label=GPS_TIMEPULSE
PB1.GPIO_PuPd=GPIO_PULLDOWN
PB1.Signal=GPXTI1
PB4.GPIOParameters=GPIO_Label
PB4.GPIO_Label=DEBUG_LED
PB4.Signal=GPIO_Output
PB5.GPIOParameters=GPIO_Label
PB5.GPIO_Label=BAT_LED
PB5.Signal=GPIO_Output
PB6.Mode=I2C
PB6.Signal=I2C1_SCL
PB7.Mode=I2C
PB7.Signal=I2C1_SDA
PF0-OSC_IN.GPIOParameters=GPIO_PuPd,GPIO_Label,GPIO_ModeDefaultEXTI
PF0-OSC_IN.GPIO_Label=USER_BUTTON
PF0-OSC_IN.GPIO_ModeDefaultEXTI=GPIO_MODE_IT_FALLING
PF0-OSC_IN.GPIO_PuPd=GPIO_PULLUP
PF0-OSC_IN.Signal=GPXTI0
PF1-OSC_OUT.GPIOParameters=GPIO_Label
PF1-OSC_OUT.GPIO_Label=GPS_LED
PF1-OSC_OUT.Signal=GPIO_Output
board=gps_logger_new

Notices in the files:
parts and their libraries:
SparkFun-Clocks: Licensing: Creative Commons ShareAlike 4.0 International - https://creativecommons.org/licenses/by-sa/4.0
microbuilder: This work is placed in the public domain, and may be freely used for commercial and non-commercial work with the following conditions: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
